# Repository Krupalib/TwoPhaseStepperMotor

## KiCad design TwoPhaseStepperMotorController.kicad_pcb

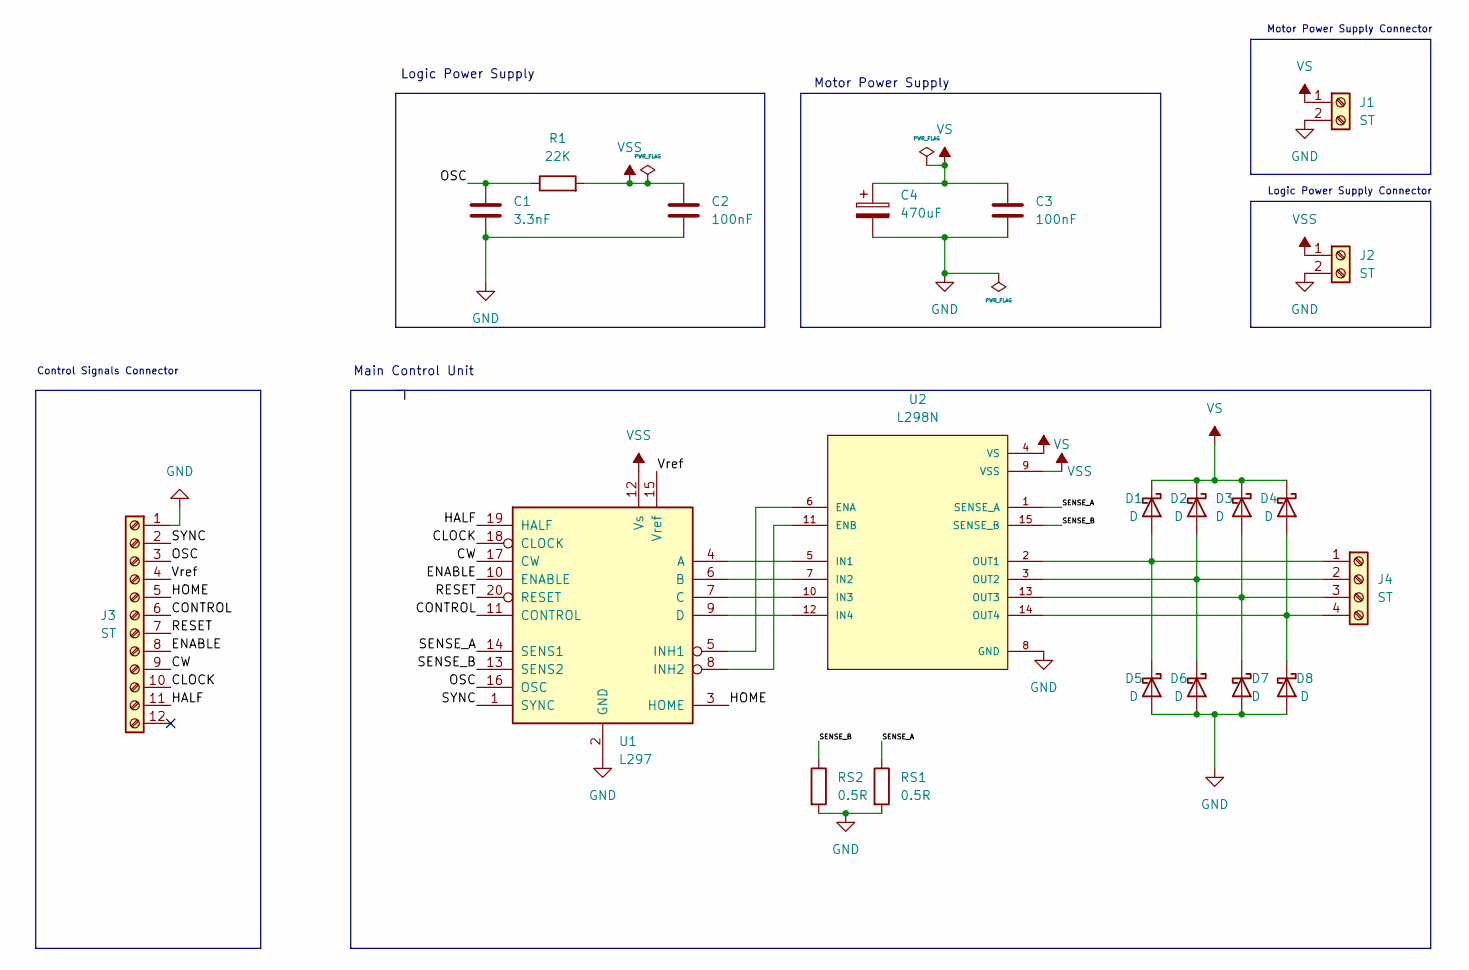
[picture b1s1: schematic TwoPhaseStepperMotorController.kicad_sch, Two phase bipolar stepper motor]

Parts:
C1: 3.3nF; C_Rect_L10.0mm_W3.0mm_P7.50mm_FKS3_FKP3
C2, C3: 100nF; C_Rect_L7.5mm_W6.5mm_P5.00mm
C4: 470uF; CP_Radial_D13.0mm_P5.00mm
D1, D2, D3, D4, D5, D6, D7, D8: D; D_DO-27_P15.24mm_Horizontal
J1, J2: ST; TerminalBlock_Phoenix_MKDS-1,5-2-5.08_1x02_P5.08mm_Horizont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
J3: ST; TerminalBlock_Phoenix_MKDS-1,5-12_1x12_P5.00mm_Horizontal
J4: ST; TerminalBlock_Phoenix_MKDS-1,5-4_1x04_P5.00mm_Horizontal
R1: 22K; R_Axial_DIN0922_L20.0mm_D9.0mm_P7.62mm_Vertical
RS1, RS2: 0.5R; R_Axial_DIN0414_L11.9mm_D4.5mm_P15.24mm_Horizontal
U1: L297; DIP-20_W7.62mm_LongPads
U2: L298N; TO127P2020X500X2100-15

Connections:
/CLOCK: J3.10, U1.18 (CLOCK)
/CONTROL: J3.6, U1.11 (CONTROL)
/CW: J3.9, U1.17 (CW)
/ENABLE: J3.8, U1.10 (ENABLE)
/HALF: J3.11, U1.19 (HALF)
/HOME: J3.5, U1.3 (HOME)
/OSC: C1.1, J3.3, R1.1, U1.16 (OSC)
/RESET: J3.7, U1.20 (RESET)
/SENSE_A: RS1.1, U1.14 (SENS1), U2.1 (SENSE_A)
/SENSE_B: RS2.1, U1.13 (SENS2), U2.15 (SENSE_B)
/SYNC: J3.2, U1.1 (SYNC)
/Vref: J3.4, U1.15 (Vref)
GND: C1.2, C2.2, C3.1, C4.2, D5.2 (A), D6.2 (A), D7.2 (A), D8.2 (A), J1.2, J2.2, J3.1, RS1.2, RS2.2, U1.2 (GND), U2.8 (GND)
unnamed: D1.2 (A), D5.1 (K), J4.1, U2.2 (OUT1)
unnamed: D2.2 (A), D6.1 (K), J4.2, U2.3 (OUT2)
unnamed: D3.2 (A), D7.1 (K), J4.3, U2.13 (OUT3)
unnamed: D4.2 (A), D8.1 (K), J4.4, U2.14 (OUT4)
unnamed: U1.4 (A), U2.5 (IN1)
unnamed: U1.6 (B), U2.7 (IN2)
unnamed: U1.7 (C), U2.10 (IN3)
unnamed: U1.9 (D), U2.12 (IN4)
unnamed: U1.5 (INH1), U2.6 (ENA)
unnamed: U1.8 (INH2), U2.11 (ENB)
VS: C3.2, C4.1, D1.1 (K), D2.1 (K), D3.1 (K), D4.1 (K), J1.1, U2.4 (VS)
VSS: C2.1, J2.1, R1.2, U1.12 (Vs), U2.9 (VSS)

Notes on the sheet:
Main Control Unit
Control Signals Connector
Logic Power Supply
Motor Power Supply Connector
Motor Power Supply
Logic Power Supply Connector

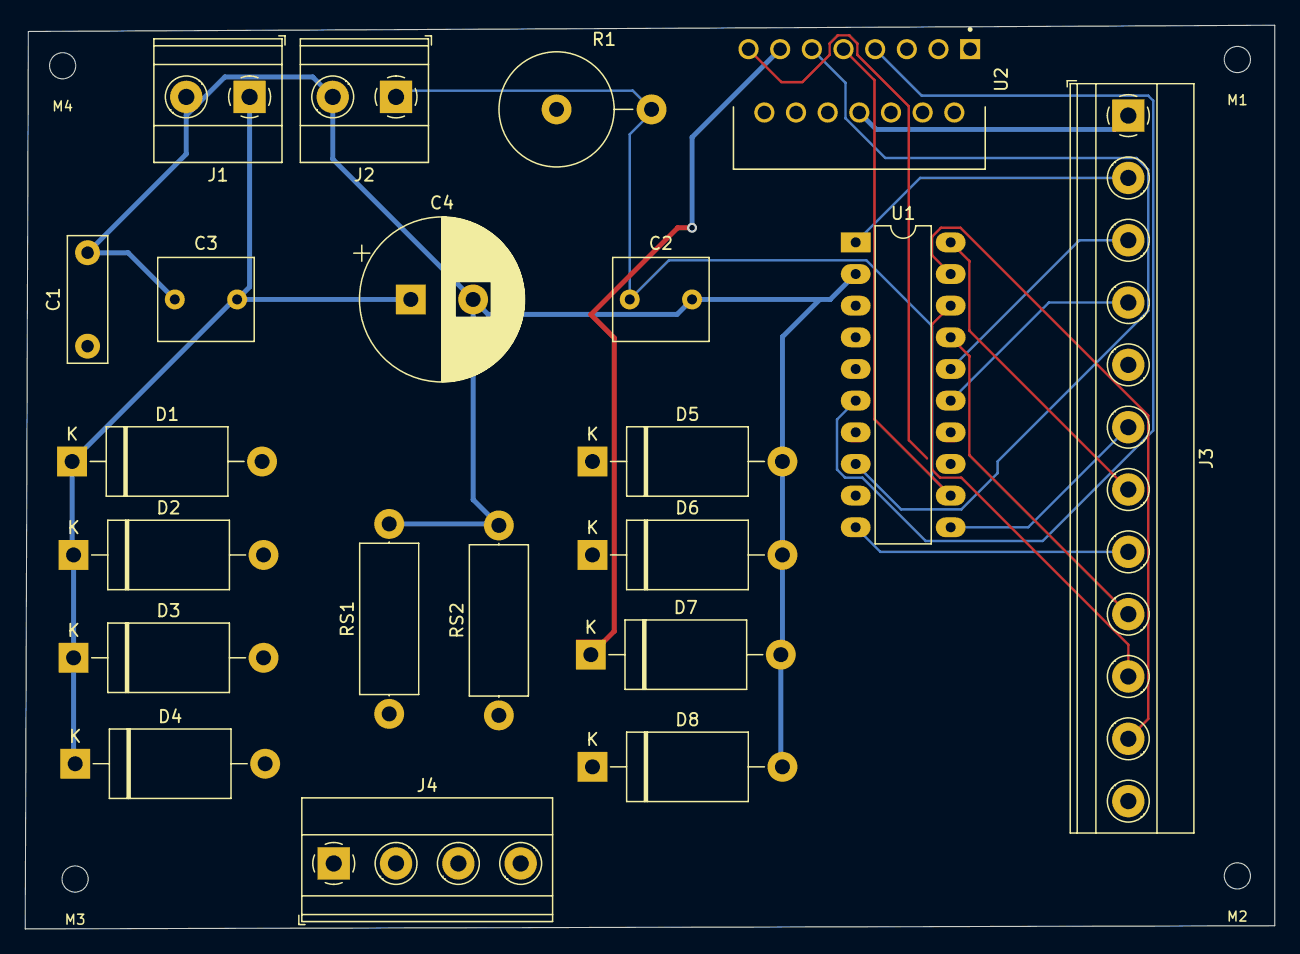
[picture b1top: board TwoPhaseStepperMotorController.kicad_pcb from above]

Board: 2 copper layers, 100.2 x 72.5 mm, 25 parts (0 on the bottom side), 25 nets.

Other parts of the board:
M1, M2, M3, M4: MountingHole_2.1mm
